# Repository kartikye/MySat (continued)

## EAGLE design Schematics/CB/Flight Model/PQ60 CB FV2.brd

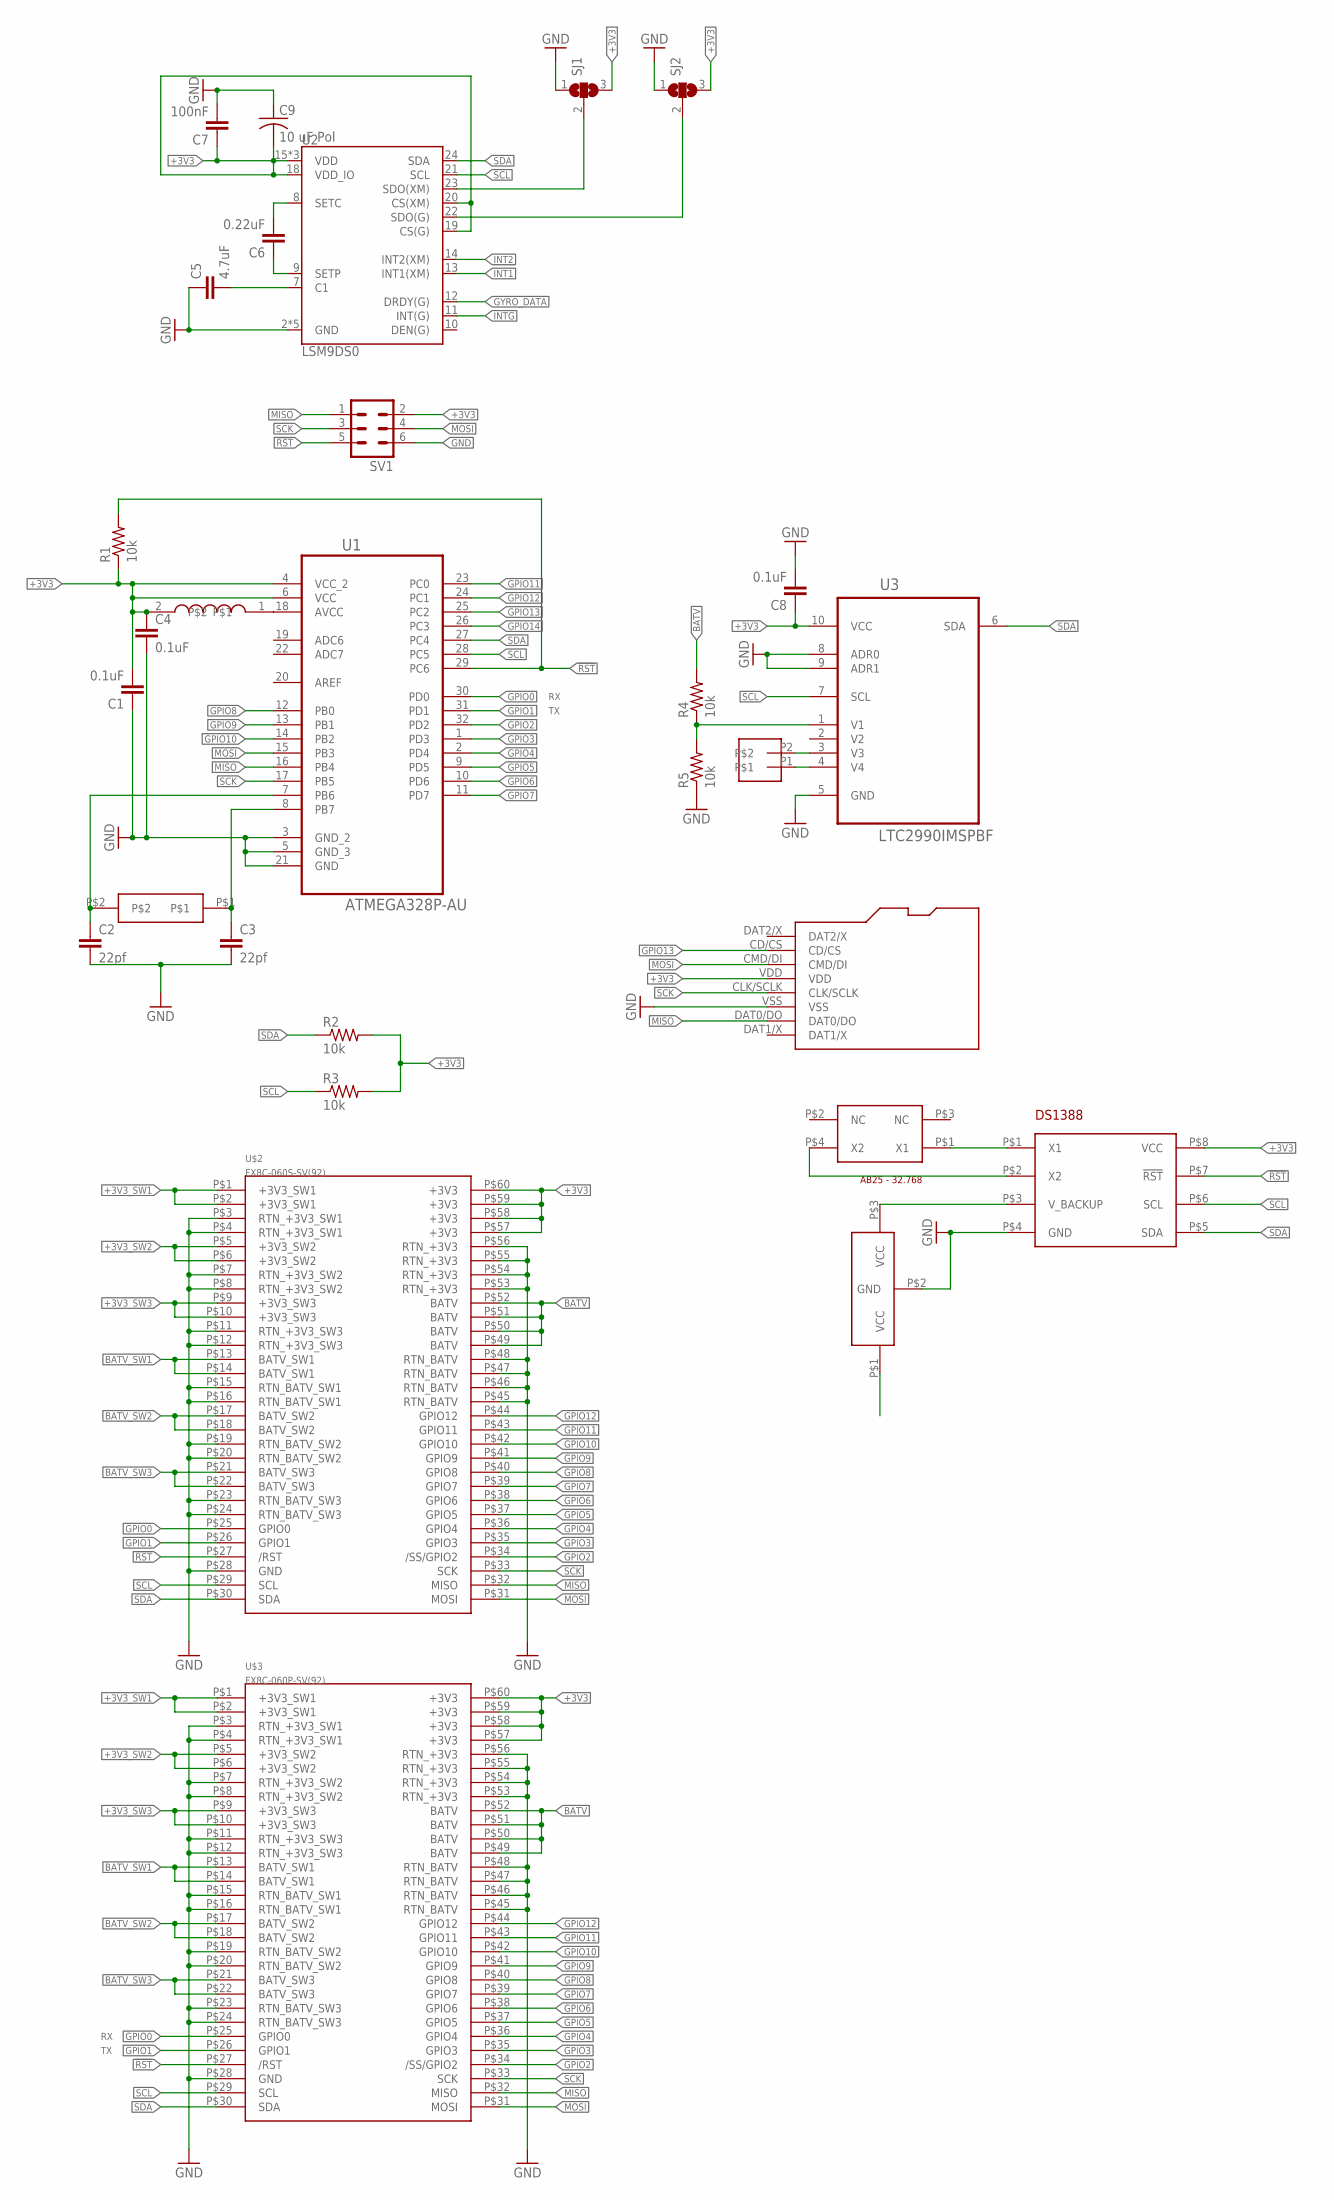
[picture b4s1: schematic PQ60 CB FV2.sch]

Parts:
C1, C4, C8: 0.1uF; C0805
C2, C3: 22pf; C0805
C5: 4.7uF; C0805
C6: 0.22uF; C0805
C7: 100nF; C0805
C9: 10 uF Pol; C0805
R1: 10k; R0805
R2, R3, R4, R5: 10k; M0805
SJ1, SJ2: SJ2W; SJ_2
SV1: MA03-2
U1: ATMEGA328P-AU; QFP80P900X900X120-32N
U2: LSM9DS0; LGA-24
U3: LTC2990IMSPBF; SOP50P490X110-10N
U$2: FX8C-060S-SV(92)
U$3: FX8C-060P-SV(92)
U$4: AB3-47699; ABM#-47699
U$5: 1210-047J
U$6: MICROSD
U$7: JST-SH-02
U$8: DS1388
U$9: AB25; ABS25
U$10: 6.8MM-BATTERY

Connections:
!RST: R1.2, SV1.5, U1.29 (PC6), U$2.P$27 (/RST), U$3.P$27 (/RST), U$8.P$7 (!RST)
+3V3: C1.2, C4.1, C7.1, C8.1, C9.2, R1.1, R2.2, R3.2, SJ1.3, SJ2.3, SV1.2, U1.4 (VCC_2), U1.6 (VCC), U2.15 (VDD), U2.16 (VDD), U2.17 (VDD), U2.18 (VDD_IO), U2.19 (CS(G)), U2.20 (CS(XM)), U3.10 (VCC), U$2.P$57 (+3V3), U$2.P$58 (+3V3), U$2.P$59 (+3V3), U$2.P$60 (+3V3), U$3.P$57 (+3V3), U$3.P$58 (+3V3), U$3.P$59 (+3V3), U$3.P$60 (+3V3), U$5.2, U$6.VDD, U$8.P$8 (VCC)
+3V3_SW1: U$2.P$1 (+3V3_SW1), U$2.P$2 (+3V3_SW1), U$3.P$1 (+3V3_SW1), U$3.P$2 (+3V3_SW1)
+3V3_SW2: U$2.P$5 (+3V3_SW2), U$2.P$6 (+3V3_SW2), U$3.P$5 (+3V3_SW2), U$3.P$6 (+3V3_SW2)
+3V3_SW3: U$2.P$9 (+3V3_SW3), U$2.P$10 (+3V3_SW3), U$3.P$9 (+3V3_SW3), U$3.P$10 (+3V3_SW3)
BATV: R4.2, U$2.P$49 (BATV), U$2.P$50 (BATV), U$2.P$51 (BATV), U$2.P$52 (BATV), U$3.P$49 (BATV), U$3.P$50 (BATV), U$3.P$51 (BATV), U$3.P$52 (BATV)
BATV_SW1: U$2.P$13 (BATV_SW1), U$2.P$14 (BATV_SW1), U$3.P$13 (BATV_SW1), U$3.P$14 (BATV_SW1)
BATV_SW2: U$2.P$17 (BATV_SW2), U$2.P$18 (BATV_SW2), U$3.P$17 (BATV_SW2), U$3.P$18 (BATV_SW2)
BATV_SW3: U$2.P$21 (BATV_SW3), U$2.P$22 (BATV_SW3), U$3.P$21 (BATV_SW3), U$3.P$22 (BATV_SW3)
GND: C1.1, C2.2, C3.2, C4.2, C5.1, C7.2, C8.2, C9.1, R5.1, SJ1.1, SJ2.1, SV1.6, U1.3 (GND_2), U1.5 (GND_3), U1.21 (GND), U2.2 (GND), U2.3 (GND), U2.4 (GND), U2.5 (GND), U2.6 (GND), U3.5 (GND), U3.8 (ADR0), U3.9 (ADR1), U$2.P$3 (RTN_+3V3_SW1), U$2.P$4 (RTN_+3V3_SW1), U$2.P$7 (RTN_+3V3_SW2), U$2.P$8 (RTN_+3V3_SW2), U$2.P$11 (RTN_+3V3_SW3), U$2.P$12 (RTN_+3V3_SW3), U$2.P$15 (RTN_BATV_SW1), U$2.P$16 (RTN_BATV_SW1), U$2.P$19 (RTN_BATV_SW2), U$2.P$20 (RTN_BATV_SW2), U$2.P$23 (RTN_BATV_SW3), U$2.P$24 (RTN_BATV_SW3), U$2.P$28 (GND), U$2.P$45 (RTN_BATV), U$2.P$46 (RTN_BATV), U$2.P$47 (RTN_BATV), U$2.P$48 (RTN_BATV), U$2.P$53 (RTN_+3V3), U$2.P$54 (RTN_+3V3), U$2.P$55 (RTN_+3V3), U$2.P$56 (RTN_+3V3), U$3.P$3 (RTN_+3V3_SW1), U$3.P$4 (RTN_+3V3_SW1), U$3.P$7 (RTN_+3V3_SW2), U$3.P$8 (RTN_+3V3_SW2), U$3.P$11 (RTN_+3V3_SW3), U$3.P$12 (RTN_+3V3_SW3), U$3.P$15 (RTN_BATV_SW1), U$3.P$16 (RTN_BATV_SW1), U$3.P$19 (RTN_BATV_SW2), U$3.P$20 (RTN_BATV_SW2), U$3.P$23 (RTN_BATV_SW3), U$3.P$24 (RTN_BATV_SW3), U$3.P$28 (GND), U$3.P$45 (RTN_BATV), U$3.P$46 (RTN_BATV), U$3.P$47 (RTN_BATV), U$3.P$48 (RTN_BATV), U$3.P$53 (RTN_+3V3), U$3.P$54 (RTN_+3V3), U$3.P$55 (RTN_+3V3), U$3.P$56 (RTN_+3V3), U$6.VSS, U$8.P$4 (GND), U$10.P$2 (GND)
GPIO0: U1.30 (PD0), U$2.P$25 (GPIO0), U$3.P$25 (GPIO0)
GPIO1: U1.31 (PD1), U$2.P$26 (GPIO1), U$3.P$26 (GPIO1)
GPIO2: U1.32 (PD2), U$2.P$34 (/SS/GPIO2), U$3.P$34 (/SS/GPIO2)
GPIO3: U1.1 (PD3), U$2.P$35 (GPIO3), U$3.P$35 (GPIO3)
GPIO4: U1.2 (PD4), U$2.P$36 (GPIO4), U$3.P$36 (GPIO4)
GPIO5: U1.9 (PD5), U$2.P$37 (GPIO5), U$3.P$37 (GPIO5)
GPIO6: U1.10 (PD6), U$2.P$38 (GPIO6), U$3.P$38 (GPIO6)
GPIO7: U1.11 (PD7), U$2.P$39 (GPIO7), U$3.P$39 (GPIO7)
GPIO8: U1.12 (PB0), U$2.P$40 (GPIO8), U$3.P$40 (GPIO8)
GPIO9: U1.13 (PB1), U$2.P$41 (GPIO9), U$3.P$41 (GPIO9)
GPIO10: U1.14 (PB2), U$2.P$42 (GPIO10), U$3.P$42 (GPIO10)
GPIO11: U1.23 (PC0), U$2.P$43 (GPIO11), U$3.P$43 (GPIO11)
GPIO12: U1.24 (PC1), U$2.P$44 (GPIO12), U$3.P$44 (GPIO12)
GPIO13: U1.25 (PC2), U$6.CD/CS
GPIO14: U1.26 (PC3)
GYRO_DATA: U2.12 (DRDY(G))
INT1: U2.13 (INT1(XM))
INT2: U2.14 (INT2(XM))
INTG: U2.11 (INT(G))
MISO: SV1.1, U1.16 (PB4), U$2.P$32 (MISO), U$3.P$32 (MISO), U$6.DAT0/DO
MOSI: SV1.4, U1.15 (PB3), U$2.P$31 (MOSI), U$3.P$31 (MOSI), U$6.CMD/DI
unnamed: R4.1, R5.2, U3.1 (V1)
unnamed: C3.1, U1.8 (PB7), U$4.P$1
unnamed: C2.1, U1.7 (PB6), U$4.P$2
unnamed: U1.18 (AVCC), U$5.1
unnamed: C5.2, U2.7 (C1)
unnamed: C6.2, U2.8 (SETC)
unnamed: C6.1, U2.9 (SETP)
unnamed: SJ1.2, U2.23 (SDO(XM))
unnamed: SJ2.2, U2.22 (SDO(G))
unnamed: U3.3 (V3), U$7.P2
unnamed: U3.4 (V4), U$7.P1
unnamed: U$8.P$1 (X1), U$9.P$1 (X1)
unnamed: U$8.P$2 (X2), U$9.P$4 (X2)
unnamed: U$8.P$3 (V_BACKUP), U$10.P$3 (VCC)
SCK: SV1.3, U1.17 (PB5), U$2.P$33 (SCK), U$3.P$33 (SCK), U$6.CLK/SCLK
SCL: R3.1, U1.28 (PC5), U2.21 (SCL), U3.7 (SCL), U$2.P$29 (SCL), U$3.P$29 (SCL), U$8.P$6 (SCL)
SDA: R2.1, U1.27 (PC4), U2.24 (SDA), U3.6 (SDA), U$2.P$30 (SDA), U$3.P$30 (SDA), U$8.P$5 (SDA)

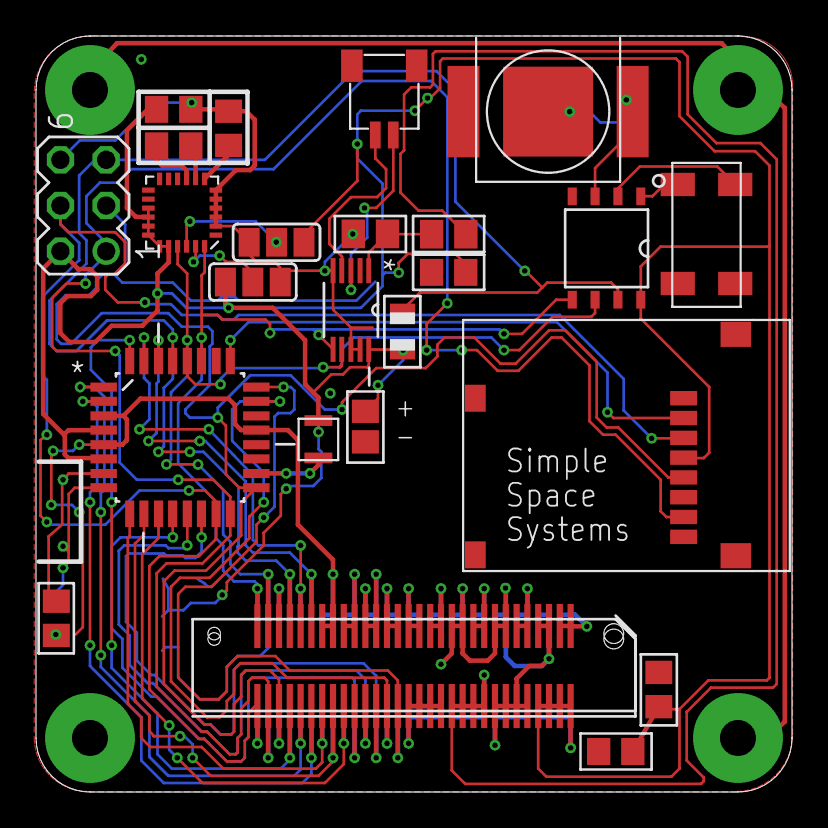
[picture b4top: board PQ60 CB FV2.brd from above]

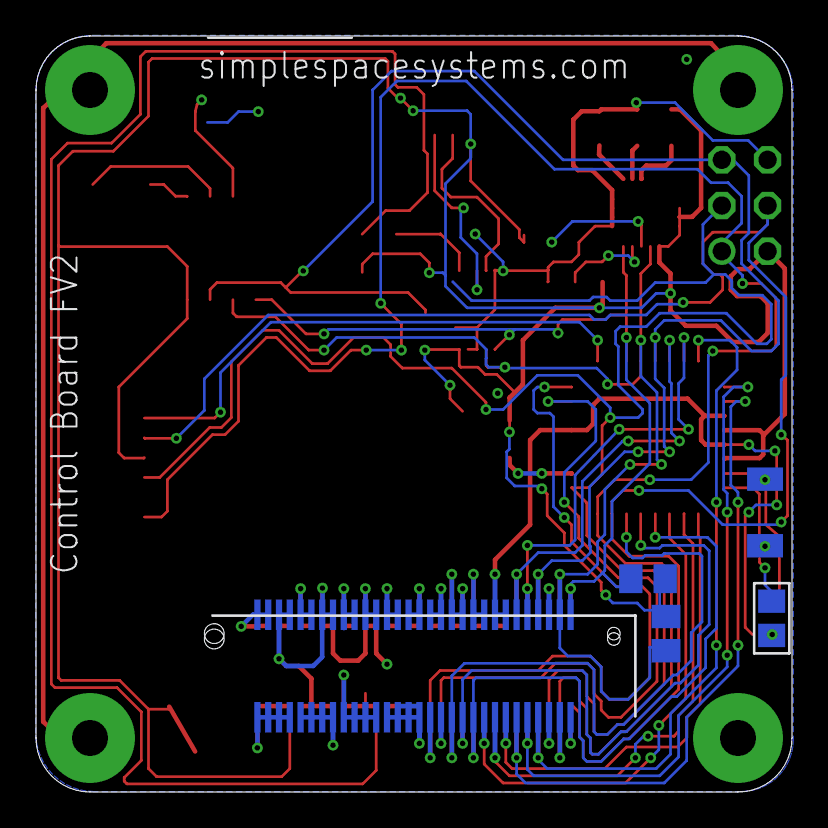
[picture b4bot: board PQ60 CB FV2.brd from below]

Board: 2 copper layers, 42.0 x 42.0 mm, 29 parts (5 on the bottom side), 43 nets.

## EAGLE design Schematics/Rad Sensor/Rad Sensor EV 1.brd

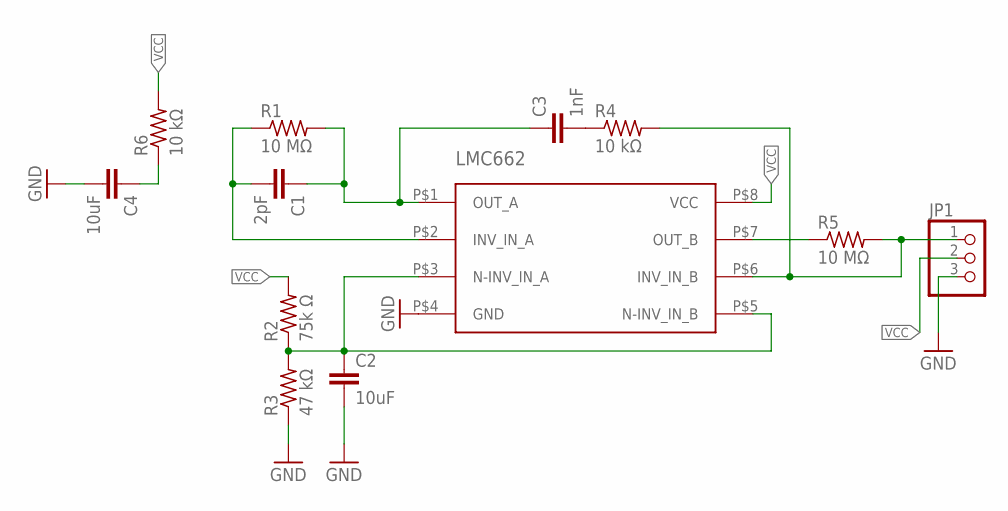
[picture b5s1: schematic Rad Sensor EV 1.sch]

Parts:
C1: 2pF; C0805
C2, C4: 10uF; C0805
C3: 1nF; C0805
JP1: PINHD-1X3; 1X03
R1, R5: 10 MΩ; R0805
R2: 75k Ω; R0805
R3: 47 kΩ; R0805
R4, R6: 10 kΩ; R0805
U$1: LMC662

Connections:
GND: C2.2, C4.2, JP1.3, R3.1, U$1.P$4 (GND)
unnamed: C1.2, R1.1, U$1.P$2 (INV_IN_A)
unnamed: C1.1, C3.1, R1.2, U$1.P$1 (OUT_A)
unnamed: C3.2, R4.1
unnamed: C2.1, R2.1, R3.2, U$1.P$3 (N-INV_IN_A), U$1.P$5 (N-INV_IN_B)
unnamed: R5.1, U$1.P$7 (OUT_B)
unnamed: JP1.1, R4.2, R5.2, U$1.P$6 (INV_IN_B)
unnamed: C4.1, R6.1
VCC: JP1.2, R2.2, R6.2, U$1.P$8 (VCC)

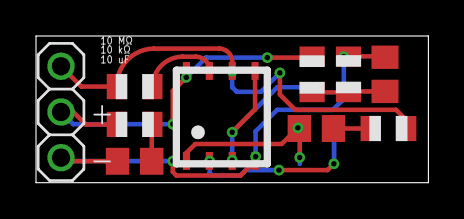
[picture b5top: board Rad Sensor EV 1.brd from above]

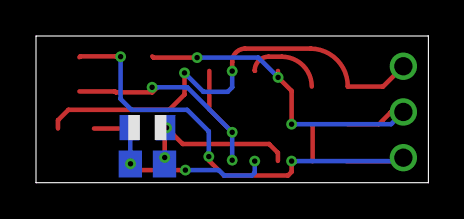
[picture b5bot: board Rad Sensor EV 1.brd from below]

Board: 2 copper layers, 21.8 x 8.2 mm, 12 parts (2 on the bottom side), 9 nets.

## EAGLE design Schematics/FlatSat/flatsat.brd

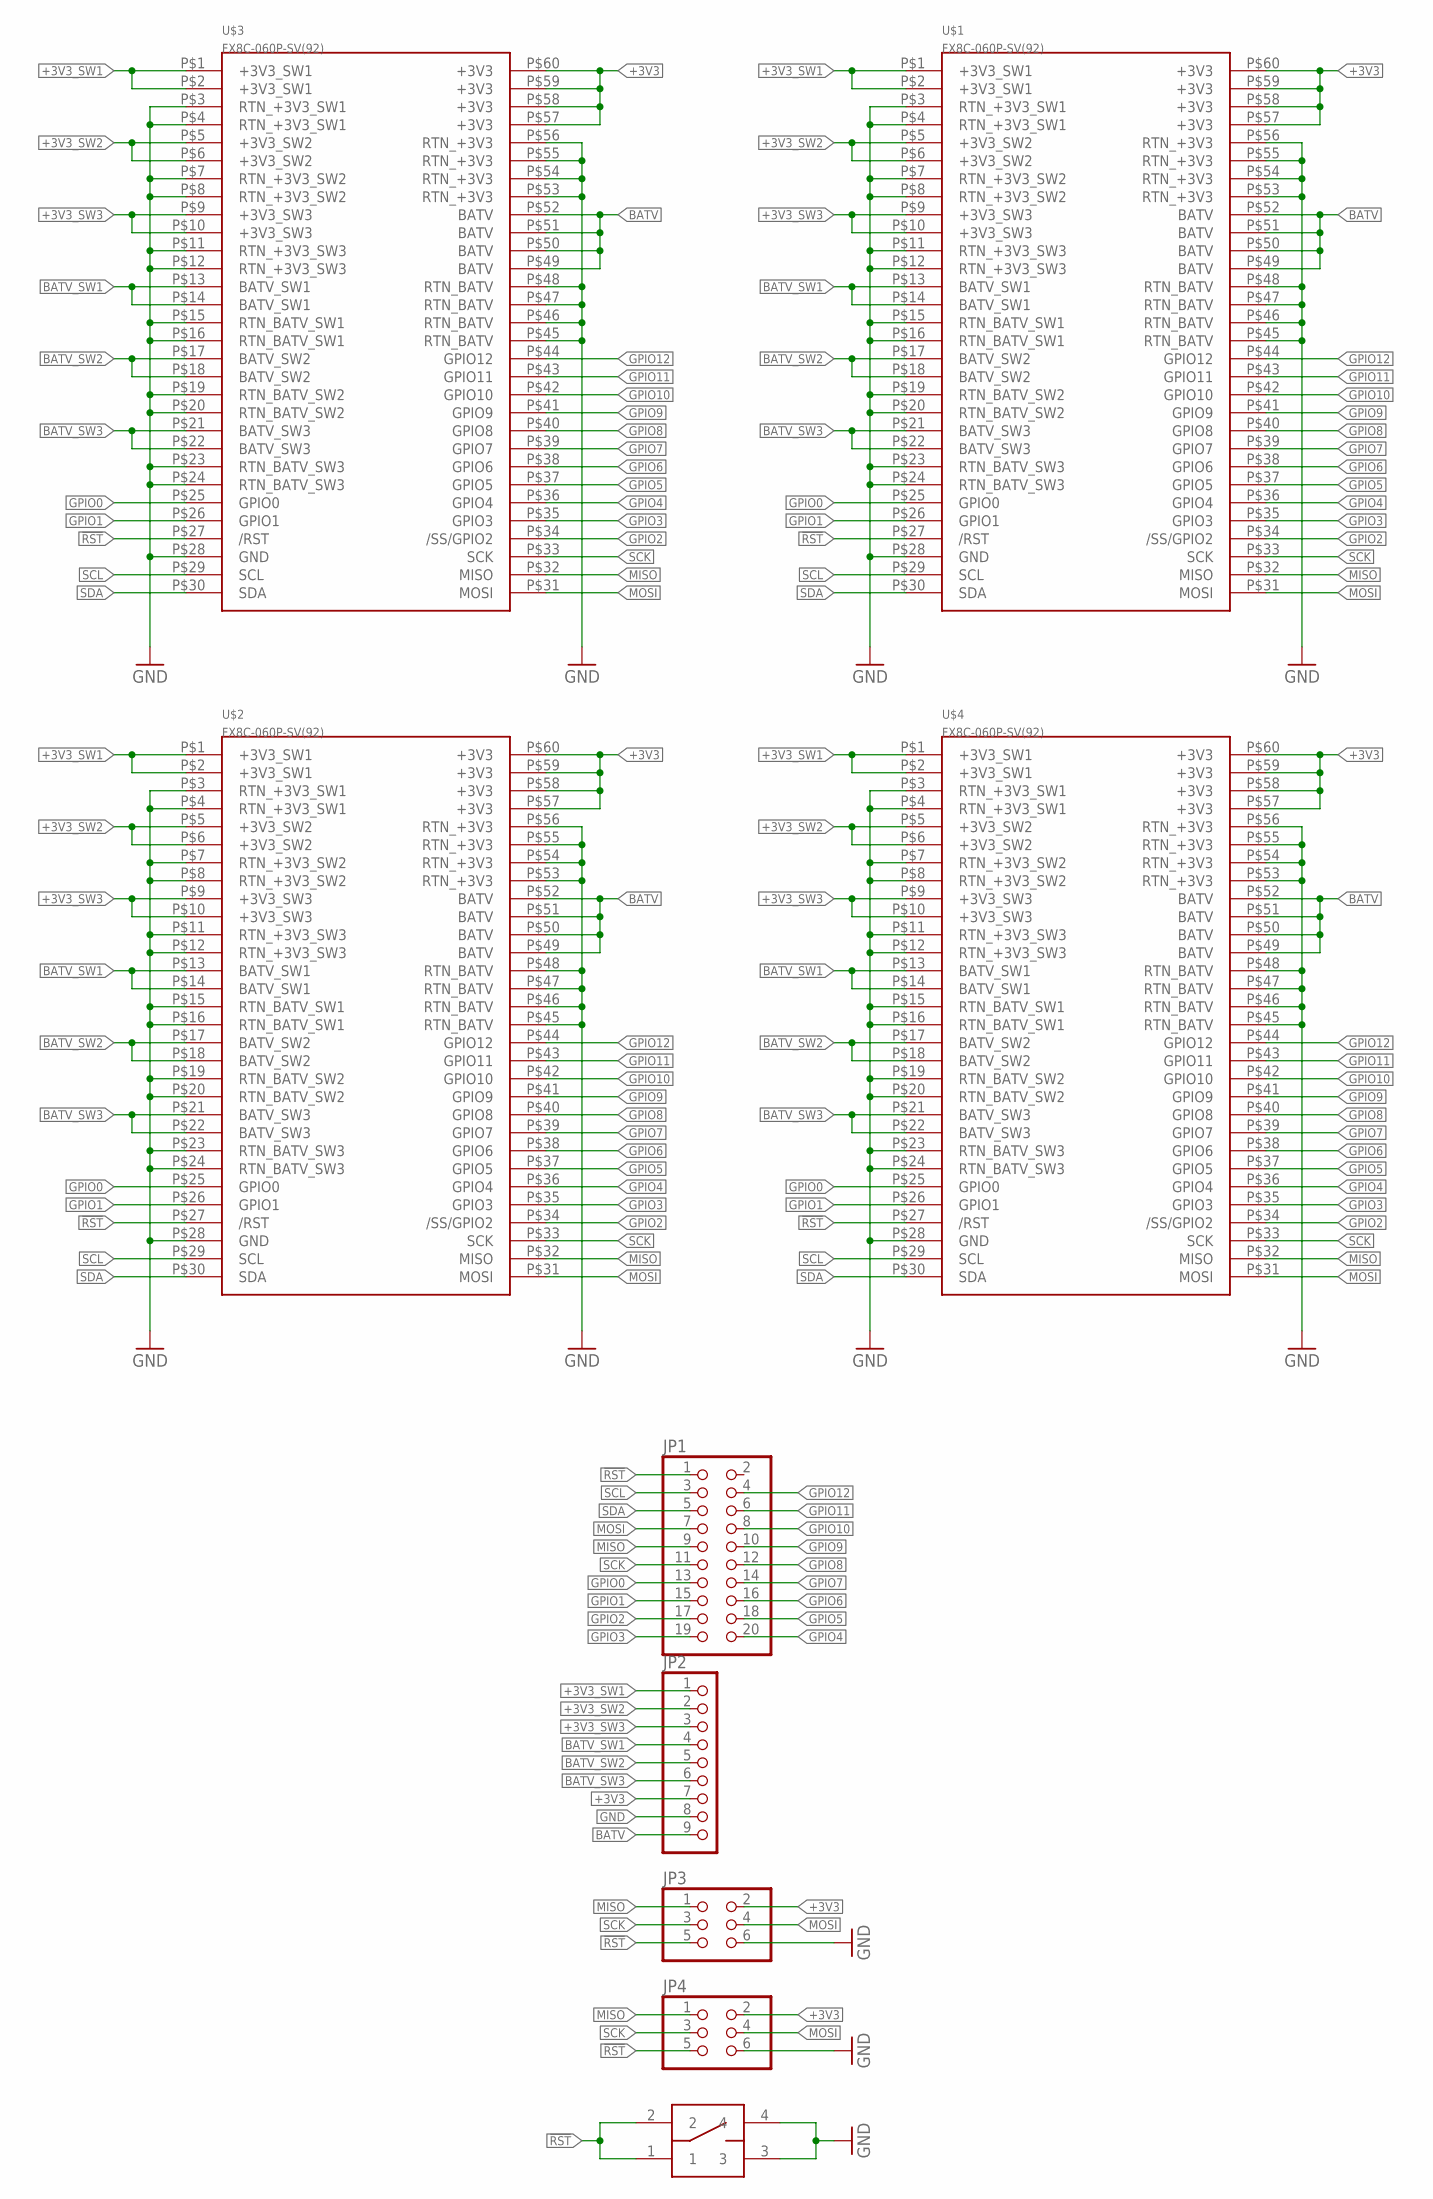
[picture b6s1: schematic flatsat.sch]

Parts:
JP1: PINHD-2X10; 2X10
JP2: PINHD-1X9; 1X09
JP3, JP4: PINHD-2X3; 2X03
U$1, U$2, U$3, U$4: FX8C-060P-SV(92)
U$5: SWITCH-TL3301

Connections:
!RST: JP1.1, JP3.5, JP4.5, U$1.P$27 (/RST), U$2.P$27 (/RST), U$3.P$27 (/RST), U$4.P$27 (/RST), U$5.1, U$5.2
+3V3: JP2.7, JP3.2, JP4.2, U$1.P$57 (+3V3), U$1.P$58 (+3V3), U$1.P$59 (+3V3), U$1.P$60 (+3V3), U$2.P$57 (+3V3), U$2.P$58 (+3V3), U$2.P$59 (+3V3), U$2.P$60 (+3V3), U$3.P$57 (+3V3), U$3.P$58 (+3V3), U$3.P$59 (+3V3), U$3.P$60 (+3V3), U$4.P$57 (+3V3), U$4.P$58 (+3V3), U$4.P$59 (+3V3), U$4.P$60 (+3V3)
+3V3_SW1: JP2.1, U$1.P$1 (+3V3_SW1), U$1.P$2 (+3V3_SW1), U$2.P$1 (+3V3_SW1), U$2.P$2 (+3V3_SW1), U$3.P$1 (+3V3_SW1), U$3.P$2 (+3V3_SW1), U$4.P$1 (+3V3_SW1), U$4.P$2 (+3V3_SW1)
+3V3_SW2: JP2.2, U$1.P$5 (+3V3_SW2), U$1.P$6 (+3V3_SW2), U$2.P$5 (+3V3_SW2), U$2.P$6 (+3V3_SW2), U$3.P$5 (+3V3_SW2), U$3.P$6 (+3V3_SW2), U$4.P$5 (+3V3_SW2), U$4.P$6 (+3V3_SW2)
+3V3_SW3: JP2.3, U$1.P$9 (+3V3_SW3), U$1.P$10 (+3V3_SW3), U$2.P$9 (+3V3_SW3), U$2.P$10 (+3V3_SW3), U$3.P$9 (+3V3_SW3), U$3.P$10 (+3V3_SW3), U$4.P$9 (+3V3_SW3), U$4.P$10 (+3V3_SW3)
BATV: JP2.9, U$1.P$49 (BATV), U$1.P$50 (BATV), U$1.P$51 (BATV), U$1.P$52 (BATV), U$2.P$49 (BATV), U$2.P$50 (BATV), U$2.P$51 (BATV), U$2.P$52 (BATV), U$3.P$49 (BATV), U$3.P$50 (BATV), U$3.P$51 (BATV), U$3.P$52 (BATV), U$4.P$49 (BATV), U$4.P$50 (BATV), U$4.P$51 (BATV), U$4.P$52 (BATV)
BATV_SW1: JP2.4, U$1.P$13 (BATV_SW1), U$1.P$14 (BATV_SW1), U$2.P$13 (BATV_SW1), U$2.P$14 (BATV_SW1), U$3.P$13 (BATV_SW1), U$3.P$14 (BATV_SW1), U$4.P$13 (BATV_SW1), U$4.P$14 (BATV_SW1)
BATV_SW2: JP2.5, U$1.P$17 (BATV_SW2), U$1.P$18 (BATV_SW2), U$2.P$17 (BATV_SW2), U$2.P$18 (BATV_SW2), U$3.P$17 (BATV_SW2), U$3.P$18 (BATV_SW2), U$4.P$17 (BATV_SW2), U$4.P$18 (BATV_SW2)
BATV_SW3: JP2.6, U$1.P$21 (BATV_SW3), U$1.P$22 (BATV_SW3), U$2.P$21 (BATV_SW3), U$2.P$22 (BATV_SW3), U$3.P$21 (BATV_SW3), U$3.P$22 (BATV_SW3), U$4.P$21 (BATV_SW3), U$4.P$22 (BATV_SW3)
GND: JP2.8, JP3.6, JP4.6, U$1.P$3 (RTN_+3V3_SW1), U$1.P$4 (RTN_+3V3_SW1), U$1.P$7 (RTN_+3V3_SW2), U$1.P$8 (RTN_+3V3_SW2), U$1.P$11 (RTN_+3V3_SW3), U$1.P$12 (RTN_+3V3_SW3), U$1.P$15 (RTN_BATV_SW1), U$1.P$16 (RTN_BATV_SW1), U$1.P$19 (RTN_BATV_SW2), U$1.P$20 (RTN_BATV_SW2), U$1.P$23 (RTN_BATV_SW3), U$1.P$24 (RTN_BATV_SW3), U$1.P$28 (GND), U$1.P$45 (RTN_BATV), U$1.P$46 (RTN_BATV), U$1.P$47 (RTN_BATV), U$1.P$48 (RTN_BATV), U$1.P$53 (RTN_+3V3), U$1.P$54 (RTN_+3V3), U$1.P$55 (RTN_+3V3), U$1.P$56 (RTN_+3V3), U$2.P$3 (RTN_+3V3_SW1), U$2.P$4 (RTN_+3V3_SW1), U$2.P$7 (RTN_+3V3_SW2), U$2.P$8 (RTN_+3V3_SW2), U$2.P$11 (RTN_+3V3_SW3), U$2.P$12 (RTN_+3V3_SW3), U$2.P$15 (RTN_BATV_SW1), U$2.P$16 (RTN_BATV_SW1), U$2.P$19 (RTN_BATV_SW2), U$2.P$20 (RTN_BATV_SW2), U$2.P$23 (RTN_BATV_SW3), U$2.P$24 (RTN_BATV_SW3), U$2.P$28 (GND), U$2.P$45 (RTN_BATV), U$2.P$46 (RTN_BATV), U$2.P$47 (RTN_BATV), U$2.P$48 (RTN_BATV), U$2.P$53 (RTN_+3V3), U$2.P$54 (RTN_+3V3), U$2.P$55 (RTN_+3V3), U$2.P$56 (RTN_+3V3), U$3.P$3 (RTN_+3V3_SW1), U$3.P$4 (RTN_+3V3_SW1), U$3.P$7 (RTN_+3V3_SW2), U$3.P$8 (RTN_+3V3_SW2), U$3.P$11 (RTN_+3V3_SW3), U$3.P$12 (RTN_+3V3_SW3), U$3.P$15 (RTN_BATV_SW1), U$3.P$16 (RTN_BATV_SW1), U$3.P$19 (RTN_BATV_SW2), U$3.P$20 (RTN_BATV_SW2), U$3.P$23 (RTN_BATV_SW3), U$3.P$24 (RTN_BATV_SW3), U$3.P$28 (GND), U$3.P$45 (RTN_BATV), U$3.P$46 (RTN_BATV), U$3.P$47 (RTN_BATV), U$3.P$48 (RTN_BATV), U$3.P$53 (RTN_+3V3), U$3.P$54 (RTN_+3V3), U$3.P$55 (RTN_+3V3), U$3.P$56 (RTN_+3V3), U$4.P$3 (RTN_+3V3_SW1), U$4.P$4 (RTN_+3V3_SW1), U$4.P$7 (RTN_+3V3_SW2), U$4.P$8 (RTN_+3V3_SW2), U$4.P$11 (RTN_+3V3_SW3), U$4.P$12 (RTN_+3V3_SW3), U$4.P$15 (RTN_BATV_SW1), U$4.P$16 (RTN_BATV_SW1), U$4.P$19 (RTN_BATV_SW2), U$4.P$20 (RTN_BATV_SW2), U$4.P$23 (RTN_BATV_SW3), U$4.P$24 (RTN_BATV_SW3), U$4.P$28 (GND), U$4.P$45 (RTN_BATV), U$4.P$46 (RTN_BATV), U$4.P$47 (RTN_BATV), U$4.P$48 (RTN_BATV), U$4.P$53 (RTN_+3V3), U$4.P$54 (RTN_+3V3), U$4.P$55 (RTN_+3V3), U$4.P$56 (RTN_+3V3), U$5.3, U$5.4
GPIO0: JP1.13, U$1.P$25 (GPIO0), U$2.P$25 (GPIO0), U$3.P$25 (GPIO0), U$4.P$25 (GPIO0)
GPIO1: JP1.15, U$1.P$26 (GPIO1), U$2.P$26 (GPIO1), U$3.P$26 (GPIO1), U$4.P$26 (GPIO1)
GPIO2: JP1.17, U$1.P$34 (/SS/GPIO2), U$2.P$34 (/SS/GPIO2), U$3.P$34 (/SS/GPIO2), U$4.P$34 (/SS/GPIO2)
GPIO3: JP1.19, U$1.P$35 (GPIO3), U$2.P$35 (GPIO3), U$3.P$35 (GPIO3), U$4.P$35 (GPIO3)
GPIO4: JP1.20, U$1.P$36 (GPIO4), U$2.P$36 (GPIO4), U$3.P$36 (GPIO4), U$4.P$36 (GPIO4)
GPIO5: JP1.18, U$1.P$37 (GPIO5), U$2.P$37 (GPIO5), U$3.P$37 (GPIO5), U$4.P$37 (GPIO5)
GPIO6: JP1.16, U$1.P$38 (GPIO6), U$2.P$38 (GPIO6), U$3.P$38 (GPIO6), U$4.P$38 (GPIO6)
GPIO7: JP1.14, U$1.P$39 (GPIO7), U$2.P$39 (GPIO7), U$3.P$39 (GPIO7), U$4.P$39 (GPIO7)
GPIO8: JP1.12, U$1.P$40 (GPIO8), U$2.P$40 (GPIO8), U$3.P$40 (GPIO8), U$4.P$40 (GPIO8)
GPIO9: JP1.10, U$1.P$41 (GPIO9), U$2.P$41 (GPIO9), U$3.P$41 (GPIO9), U$4.P$41 (GPIO9)
GPIO10: JP1.8, U$1.P$42 (GPIO10), U$2.P$42 (GPIO10), U$3.P$42 (GPIO10), U$4.P$42 (GPIO10)
GPIO11: JP1.6, U$1.P$43 (GPIO11), U$2.P$43 (GPIO11), U$3.P$43 (GPIO11), U$4.P$43 (GPIO11)
GPIO12: JP1.4, U$1.P$44 (GPIO12), U$2.P$44 (GPIO12), U$3.P$44 (GPIO12), U$4.P$44 (GPIO12)
MISO: JP1.9, JP3.1, JP4.1, U$1.P$32 (MISO), U$2.P$32 (MISO), U$3.P$32 (MISO), U$4.P$32 (MISO)
MOSI: JP1.7, JP3.4, JP4.4, U$1.P$31 (MOSI), U$2.P$31 (MOSI), U$3.P$31 (MOSI), U$4.P$31 (MOSI)
SCK: JP1.11, JP3.3, JP4.3, U$1.P$33 (SCK), U$2.P$33 (SCK), U$3.P$33 (SCK), U$4.P$33 (SCK)
SCL: JP1.3, U$1.P$29 (SCL), U$2.P$29 (SCL), U$3.P$29 (SCL), U$4.P$29 (SCL)
SDA: JP1.5, U$1.P$30 (SDA), U$2.P$30 (SDA), U$3.P$30 (SDA), U$4.P$30 (SDA)

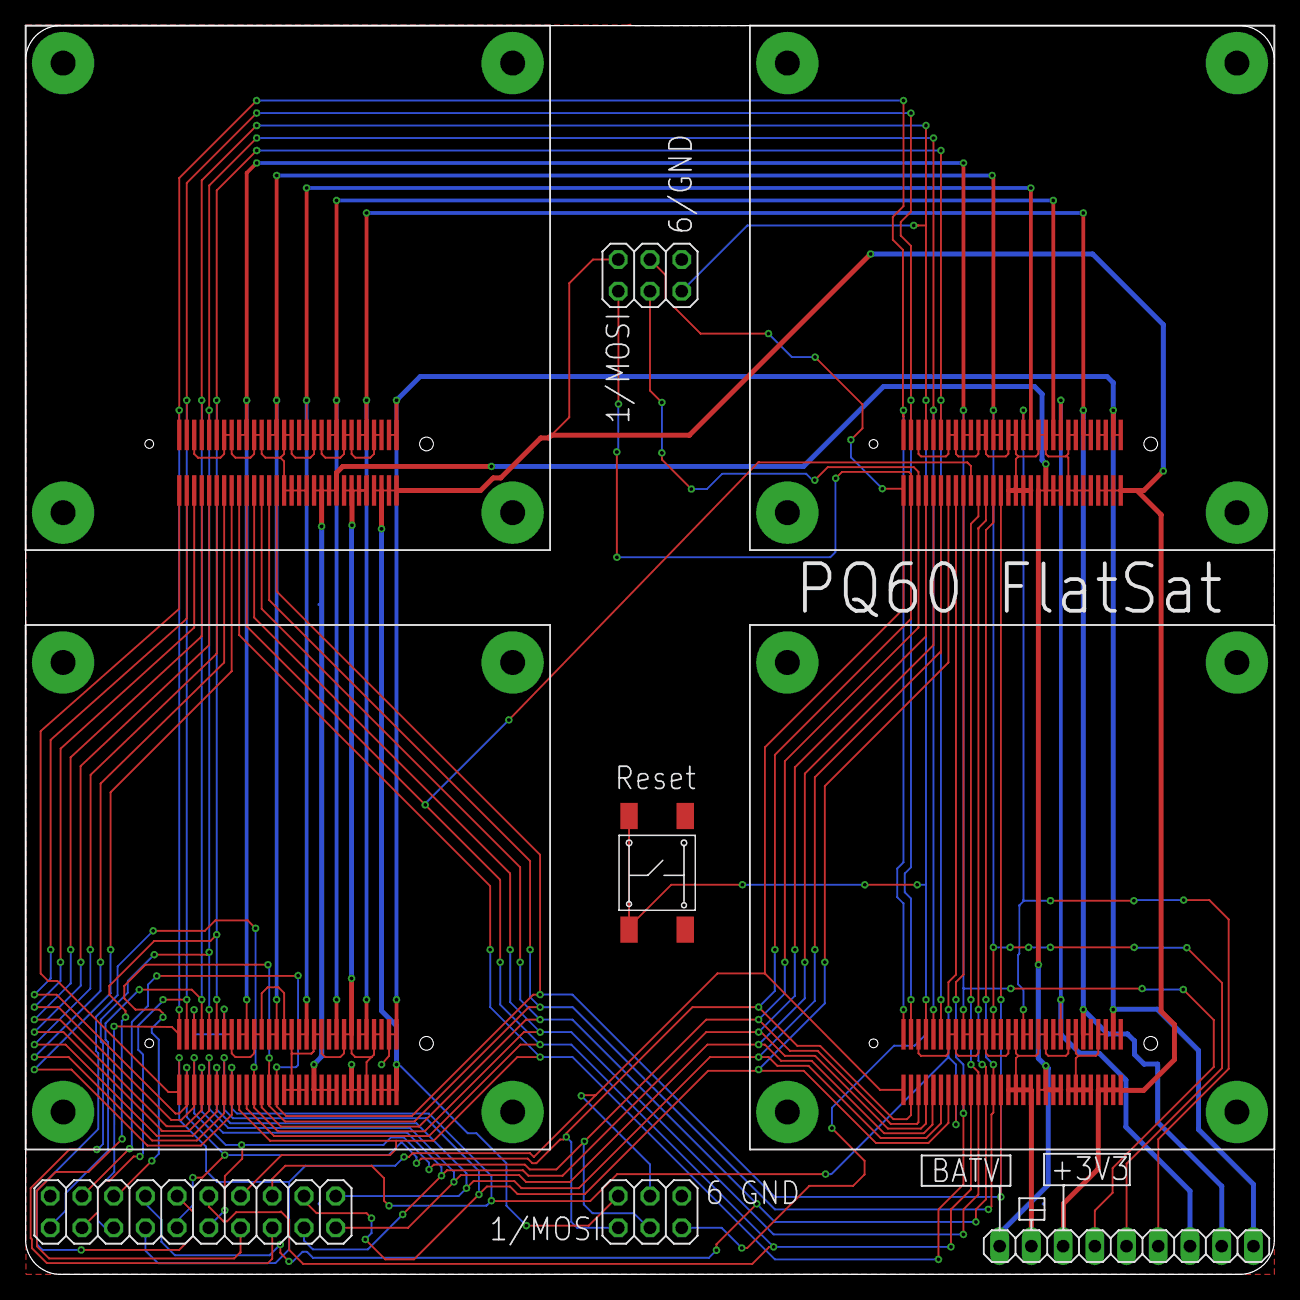
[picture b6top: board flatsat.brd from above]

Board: 2 copper layers, 100.0 x 100.0 mm, 9 parts (0 on the bottom side), 28 nets.

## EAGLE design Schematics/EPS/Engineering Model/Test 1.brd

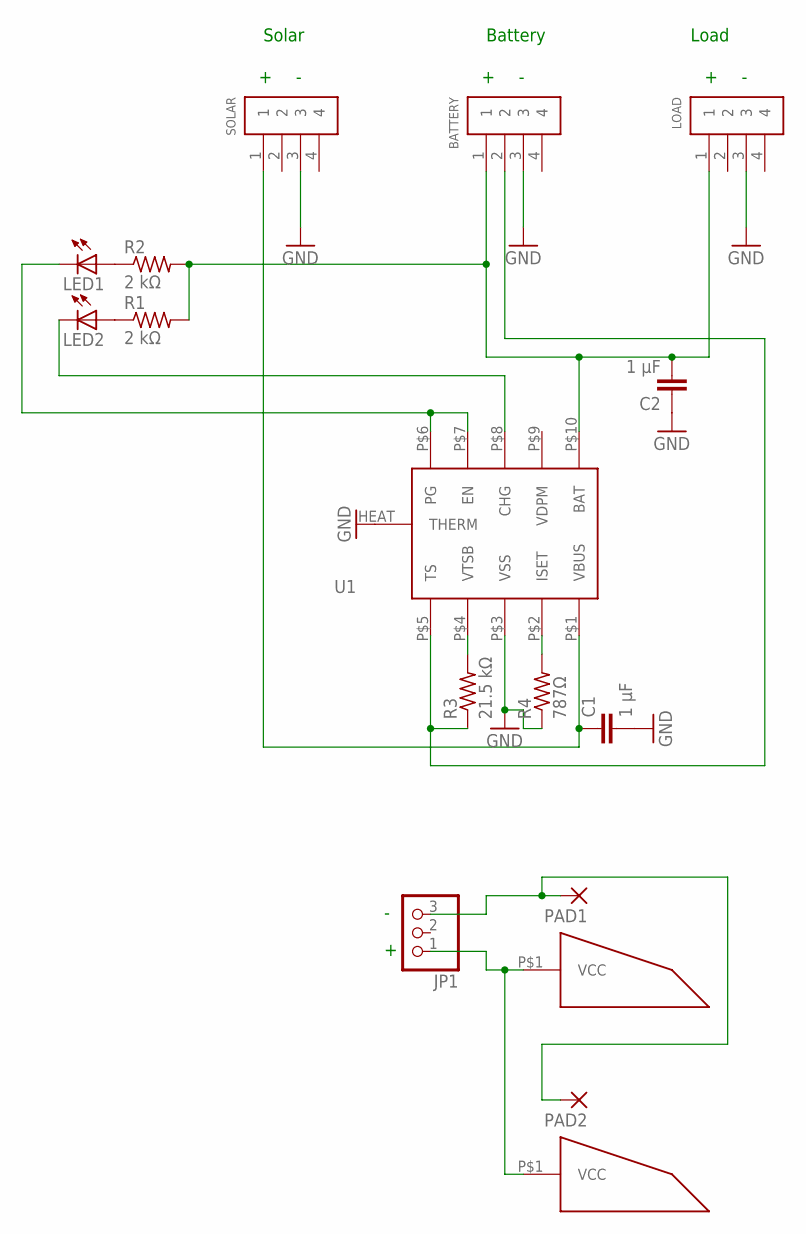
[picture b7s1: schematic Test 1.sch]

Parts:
BATTERY: 1X4-CLEANBIG; 1X04-CLEANBIG
C1, C2: 1 µF; C0805
JP1: PINHD-1X3; 1X03
LED1, LED2: LEDCHIP-LED0805; CHIP-LED0805
LOAD: 1X4-CLEANBIG; 1X04-CLEANBIG
PAD1, PAD2: SMD2; SMD1,27-2,54
R1, R2: 2 kΩ; R0805
R3: 21.5 kΩ; R0805
R4: 787Ω; R0805
SOLAR: 1X4-CLEANBIG; 1X04-CLEANBIG
U1: BQ24210
U$1, U$2: TRISOLX

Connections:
GND: BATTERY.3, C1.2, C2.1, LOAD.3, R4.1, SOLAR.3, U1.HEAT (THERM), U1.P$3 (VSS)
unnamed: LED1.C, U1.P$6 (PG), U1.P$7 (EN)
unnamed: BATTERY.2, R3.1, U1.P$5 (TS)
unnamed: BATTERY.1, C2.2, LOAD.1, R1.2, R2.2, U1.P$10 (BAT)
unnamed: C1.1, SOLAR.1, U1.P$1 (VBUS)
unnamed: LED1.A, R2.1
unnamed: LED2.A, R1.1
unnamed: R3.2, U1.P$4 (VTSB)
unnamed: R4.2, U1.P$2 (ISET)
unnamed: LED2.C, U1.P$8 (CHG)
unnamed: JP1.3, PAD1.1, PAD2.1
unnamed: JP1.1, U$1.P$1, U$2.P$1

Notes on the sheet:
Battery
Load
Solar

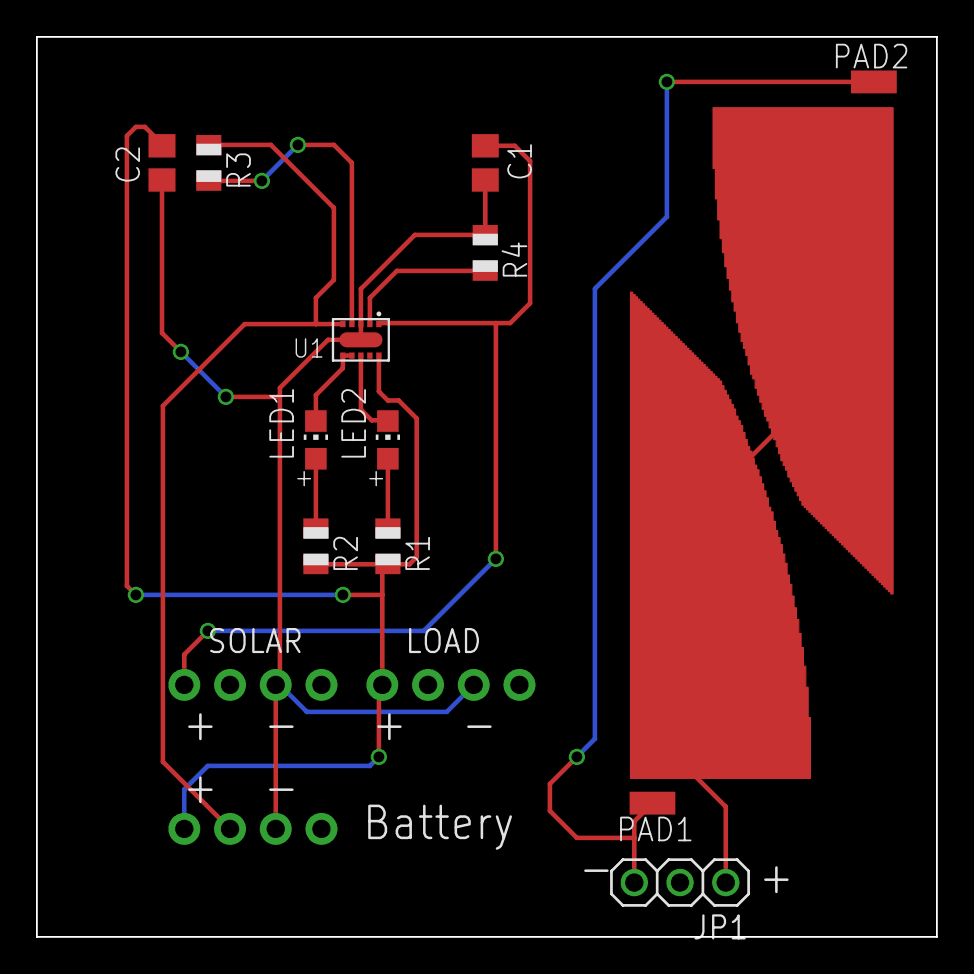
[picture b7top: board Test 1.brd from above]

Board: 2 copper layers, 50.0 x 50.0 mm, 17 parts (0 on the bottom side), 12 nets.

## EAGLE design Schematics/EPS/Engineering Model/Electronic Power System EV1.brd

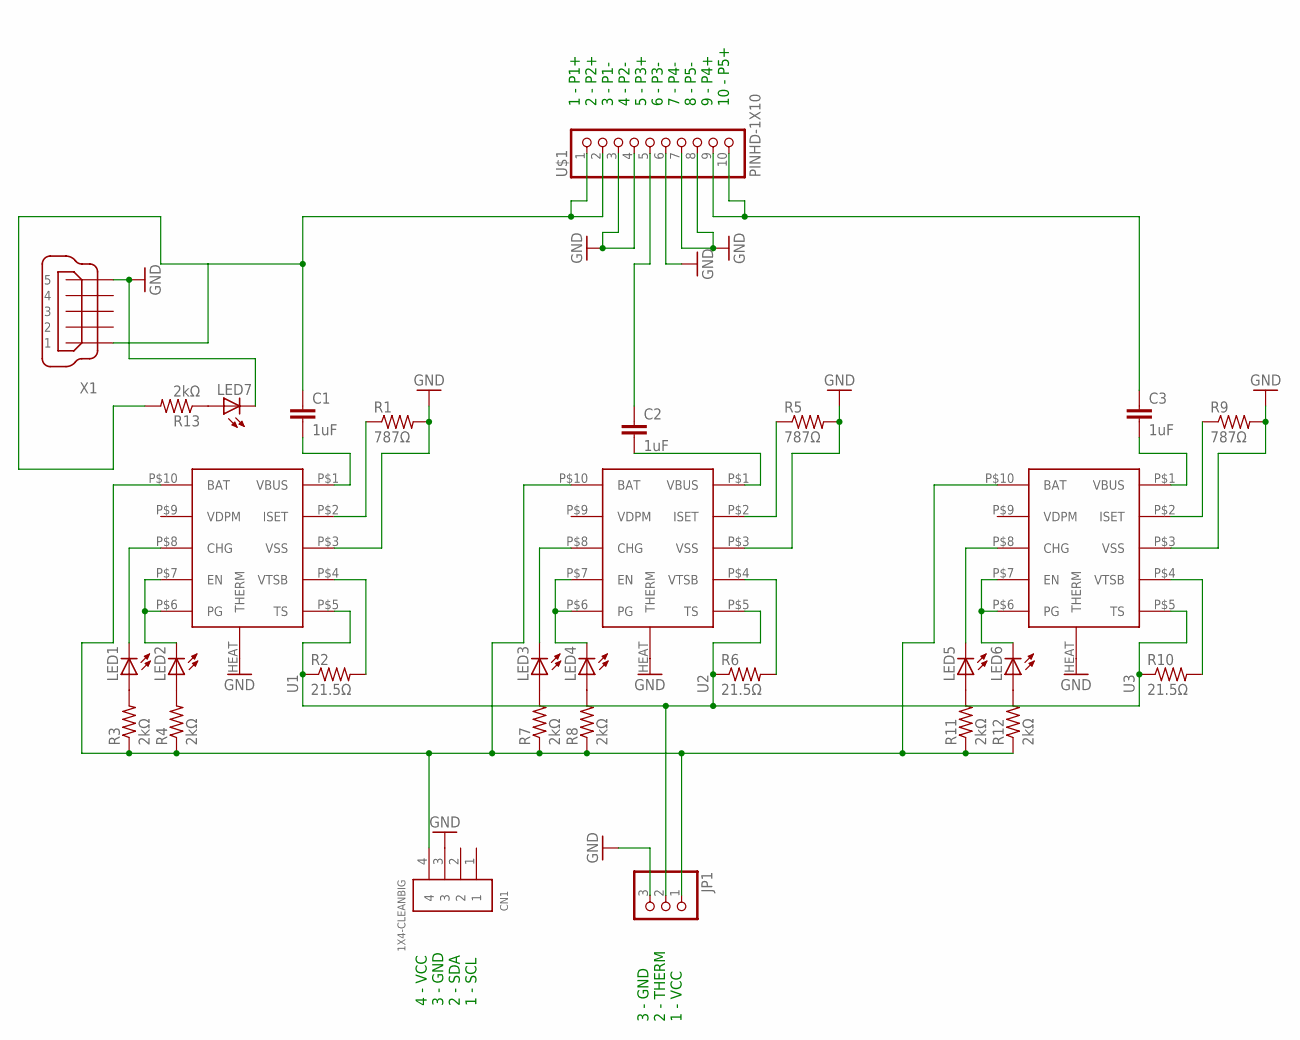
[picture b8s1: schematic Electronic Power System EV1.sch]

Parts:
C1, C2, C3: 1uF; C0805
CN1: 1X4-CLEANBIG; 1X04-CLEANBIG
JP1: PINHD-1X3; 1X03
LED1, LED2, LED3, LED4, LED5, LED6, LED7: LEDCHIPLED_0805; CHIPLED_0805
R1, R5, R9: 787Ω; R0805
R2, R6, R10: 21.5Ω; R0805
R3, R4, R7, R8, R11, R12, R13: 2kΩ; R0805
U1, U2, U3: BQ24210
U$1: PINHD-1X10; 1X10-BIG
X1: MINI-USB-UX60A-MB-5ST; UX60A-MB-5ST

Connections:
GND: CN1.3, JP1.3, LED7.C, R1.2, R5.2, R9.2, U1.HEAT (THERM), U1.P$3 (VSS), U2.HEAT (THERM), U2.P$3 (VSS), U3.HEAT (THERM), U3.P$3 (VSS), U$1.3, U$1.4, U$1.6, U$1.7, U$1.8, X1.5
unnamed: LED1.C, U1.P$8 (CHG)
unnamed: R10.2, U3.P$4 (VTSB)
unnamed: C1.2, U1.P$1 (VBUS)
unnamed: C2.2, U2.P$1 (VBUS)
unnamed: R6.2, U2.P$4 (VTSB)
unnamed: CN1.4, JP1.1, R3.1, R4.1, R7.1, R8.1, R11.1, R12.1, U1.P$10 (BAT), U2.P$10 (BAT), U3.P$10 (BAT)
unnamed: C3.2, U3.P$1 (VBUS)
unnamed: R2.2, U1.P$4 (VTSB)
unnamed: LED2.C, U1.P$6 (PG), U1.P$7 (EN)
unnamed: LED4.C, U2.P$6 (PG), U2.P$7 (EN)
unnamed: LED6.C, U3.P$6 (PG), U3.P$7 (EN)
unnamed: R5.1, U2.P$2 (ISET)
unnamed: R1.1, U1.P$2 (ISET)
unnamed: R9.1, U3.P$2 (ISET)
unnamed: LED3.C, U2.P$8 (CHG)
unnamed: LED1.A, R3.2
unnamed: LED5.C, U3.P$8 (CHG)
unnamed: C1.1, R13.2, U$1.1, U$1.2, X1.1
unnamed: LED2.A, R4.2
unnamed: LED3.A, R7.2
unnamed: LED4.A, R8.2
unnamed: LED5.A, R11.2
unnamed: LED6.A, R12.2
unnamed: C2.1, U$1.5
unnamed: JP1.2, R2.1, R6.1, R10.1, U1.P$5 (TS), U2.P$5 (TS), U3.P$5 (TS)
unnamed: C3.1, U$1.9, U$1.10
unnamed: LED7.A, R13.1

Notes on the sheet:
1 - P1+ 2 - P2+ 3 - P1- 4 - P2- 5 - P3+ 6 - P3- 7 - P4- 8 - P5- 9 - P4+ 10 - P5+
3 - GND 2 - THERM 1 - VCC
4 - VCC 3 - GND 2 - SDA 1 - SCL

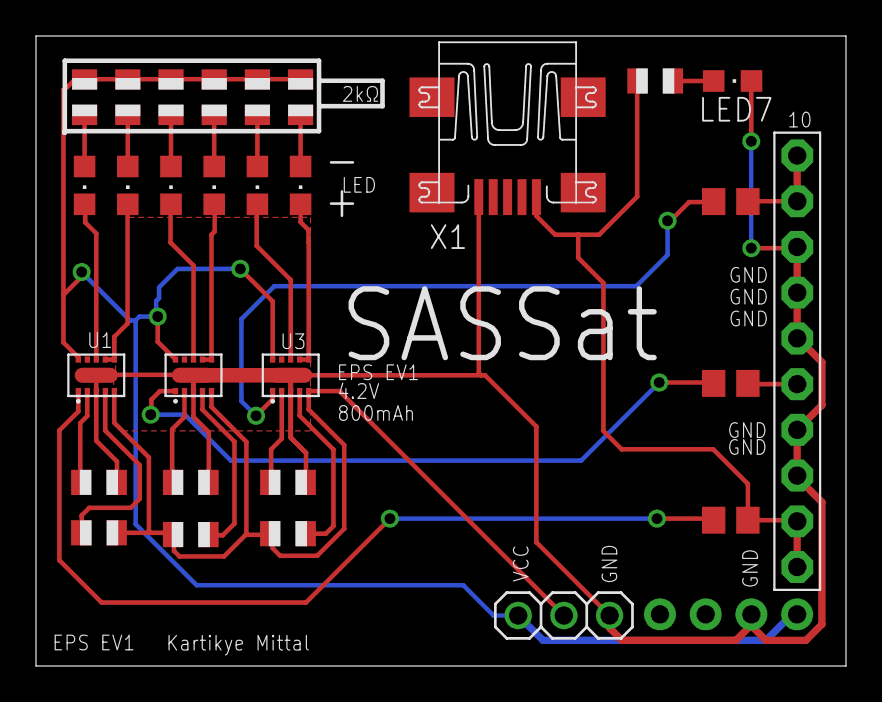
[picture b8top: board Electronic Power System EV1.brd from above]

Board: 2 copper layers, 45.0 x 35.0 mm, 30 parts (0 on the bottom side), 28 nets.

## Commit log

2015-04-18 :confetti_ball: Added .gitattributes & .gitignore files
2015-04-18 Initial
2015-04-18 Initial Code
2015-04-18 New Communication Code
2015-04-18 Revert "New Communication Code"
    This reverts commit 1bc61242c754332bd05d698dd5e2b02570b8d479.
2015-04-18 Revert "Revert "New Communication Code""
    This reverts commit f9d97fe2db5782458990c85c518269c242d87f1a.
2015-04-18 Revert "Revert "Revert "New Communication Code"""
    This reverts commit 57f633d7fe8f4710fa478d5c88a7c094c4a9add2.
2015-04-18 new code
2015-04-18 Removed GPS
2015-04-18 Removes Senor files
2015-04-18 Removed Uneccesary Comments
2015-04-21 Radio Head Trial
2015-04-21 Added RadioHead Library
2015-04-21 Organization
2015-05-28 Solar Panel and EPS Test
2015-05-28 Panel
    edde
2015-06-22 Structure
2015-06-28 New EPS
2015-06-28 Added Frame
2015-07-02 EPS.brd
2015-07-04 Complteded routing
2015-08-25 many many things
2015-09-08 Upddates
2015-12-20 many changes
